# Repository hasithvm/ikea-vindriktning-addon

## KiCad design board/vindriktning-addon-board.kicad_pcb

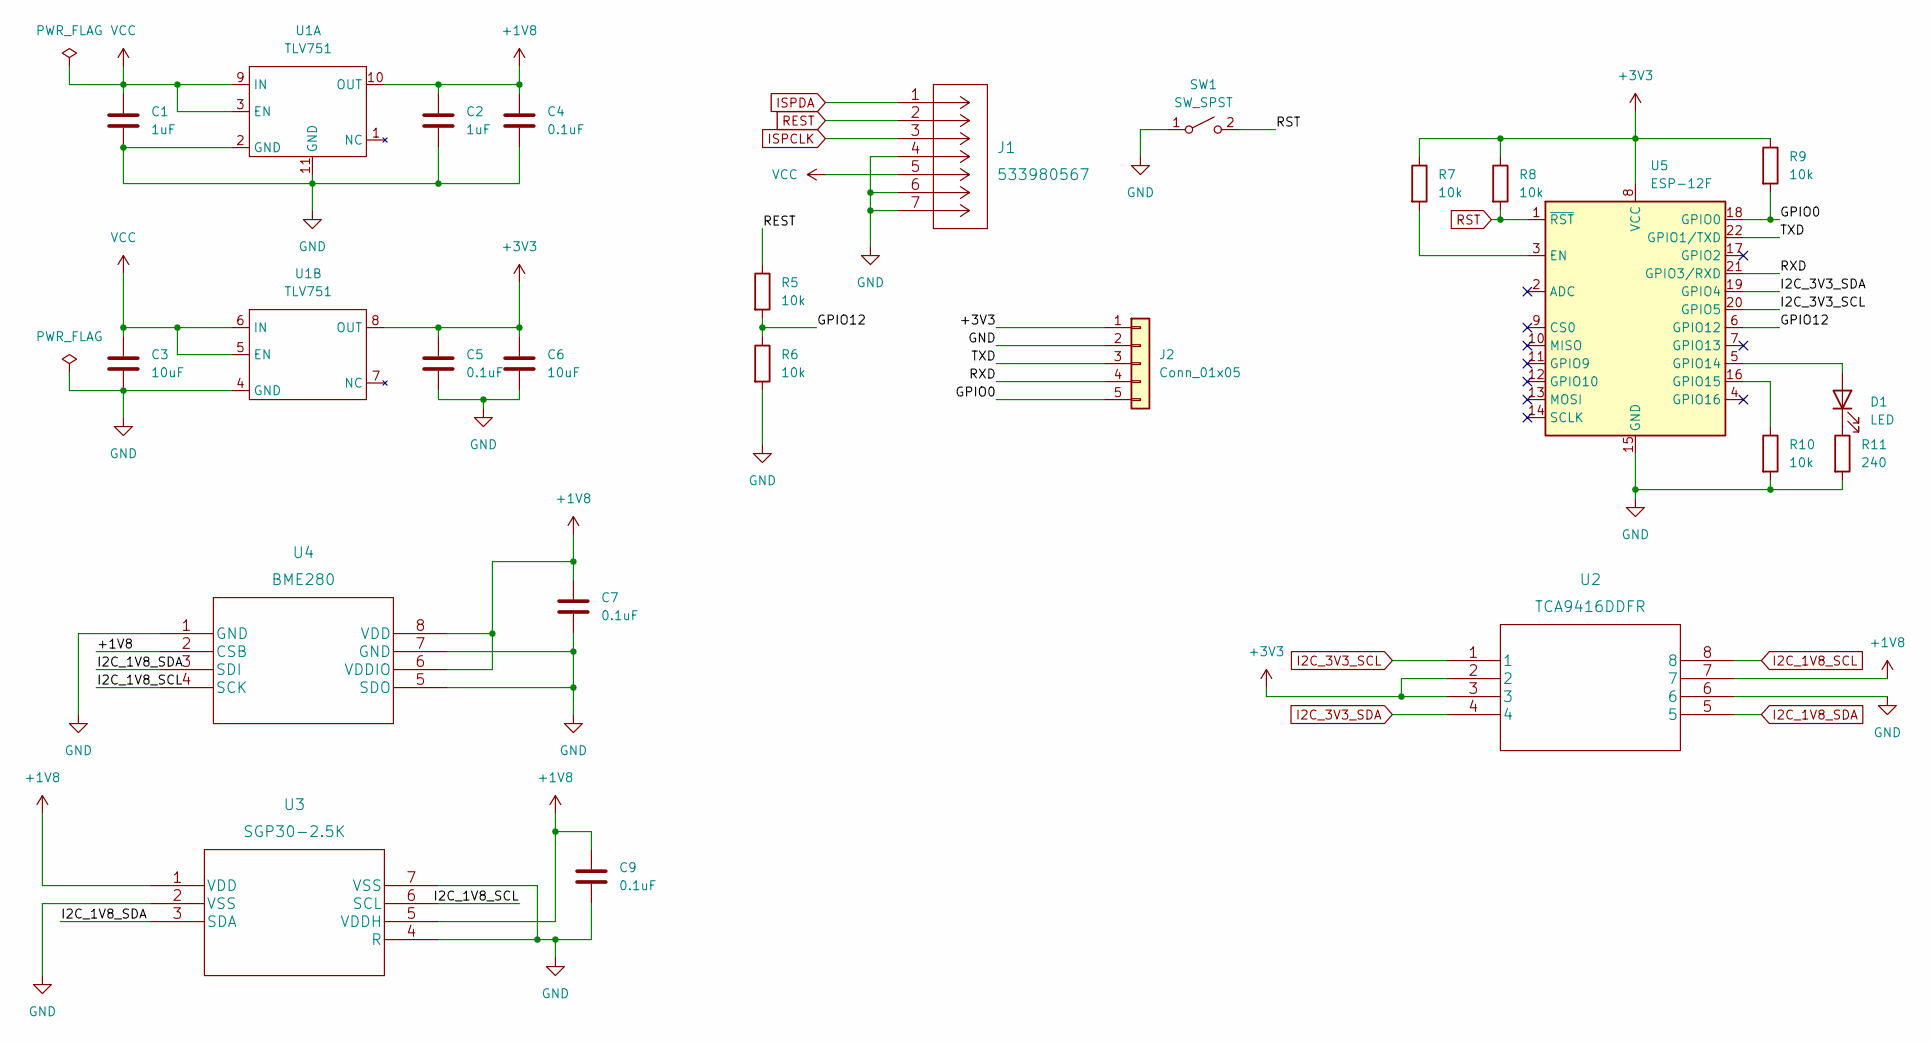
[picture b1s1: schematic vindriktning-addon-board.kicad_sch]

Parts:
C1, C2: 1uF; C_0603_1608Metric
C3, C6: 10uF; C_0805_2012Metric
C4, C5, C7, C9: 0.1uF; C_0603_1608Metric
D1: LED; LED_0603_1608Metric
J1: 533980567
J2: Conn_01x05; PinHeader_1x05_P2.54mm_Vertical
R5, R6, R7, R8, R9, R10: 10k; R_0603_1608Metric
R11: 240; R_0603_1608Metric
SW1: SW_SPST; SW_SPST_EVQP7A
U1: TLV751; TLV75101PDSQR
U2: TCA9416DDFR
U3: SGP30-2.5K
U4: BME280
U5: ESP-12F; ESP-12E

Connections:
+1V8: C2.1, C4.1, C7.1, C9.1, U1.10 (OUT), U2.7, U3.1 (VDD), U3.5 (VDDH), U4.2 (CSB), U4.6 (VDDIO), U4.8 (VDD)
+3V3: C5.1, C6.1, J2.1, R7.1, R8.1, R9.1, U1.8 (OUT), U2.2, U2.3, U5.8 (VCC)
/GPIO0: J2.5, R9.2, U5.18 (GPIO0)
/GPIO12: R5.2, R6.1, U5.6 (GPIO12)
/RXD: J2.4, U5.21 (GPIO3/RXD)
/TXD: J2.3, U5.22 (GPIO1/TXD)
GND: C1.2, C2.2, C3.2, C4.2, C5.2, C6.2, C7.2, C9.2, J1.4, J1.6, J1.7, J2.2, R6.2, R10.2, R11.2, SW1.1 (A), U1.2 (GND), U1.4 (GND), U1.11 (GND), U2.6, U3.2 (VSS), U3.4 (R), U3.7 (VSS), U4.1 (GND), U4.5 (SDO), U4.7 (GND), U5.15 (GND)
I2C_1V8_SCL: U2.8, U3.6 (SCL), U4.4 (SCK)
I2C_1V8_SDA: U2.5, U3.3 (SDA), U4.3 (SDI)
I2C_3V3_SCL: U2.1, U5.20 (GPIO5)
I2C_3V3_SDA: U2.4, U5.19 (GPIO4)
ISPCLK: J1.3
ISPDA: J1.1
unnamed: D1.1 (K), R11.1
unnamed: D1.2 (A), U5.5 (GPIO14)
unnamed: R7.2, U5.3 (EN)
unnamed: R10.1, U5.16 (GPIO15)
REST: J1.2, R5.1
RST: R8.2, SW1.2 (B), U5.1 (~RST)
VCC: C1.1, C3.1, J1.5, U1.3 (EN), U1.5 (EN), U1.6 (IN), U1.9 (IN)

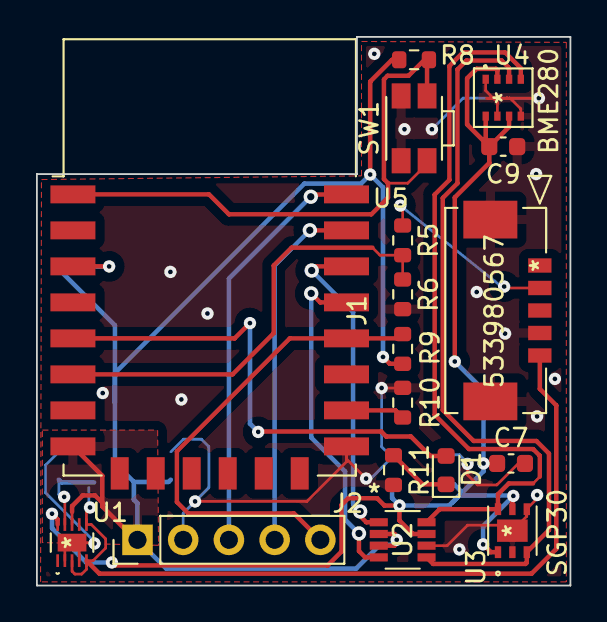
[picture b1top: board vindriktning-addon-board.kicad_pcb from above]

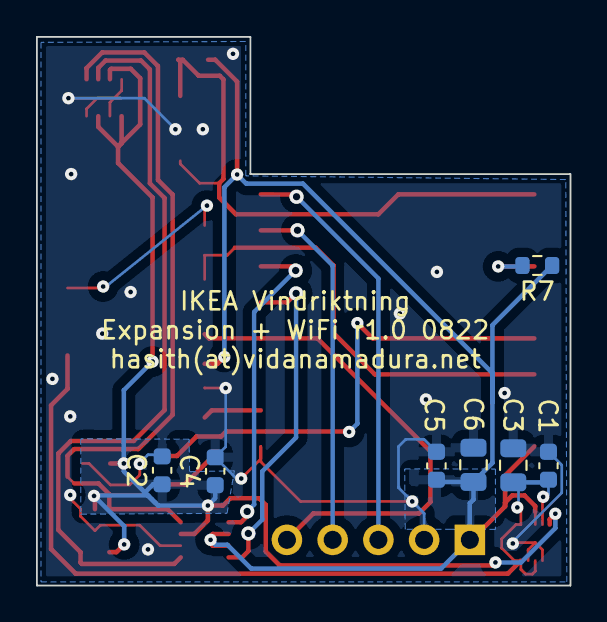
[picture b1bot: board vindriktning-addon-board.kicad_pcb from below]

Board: 2 copper layers, 29.6 x 30.5 mm, 24 parts (7 on the bottom side), 18 nets.

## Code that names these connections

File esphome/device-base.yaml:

# Base YAML config for the Vindriktning add-on board
i2c:
  sda: GPIO4
  scl: GPIO5
  scan: true
  id: bus_sensors

uart:
  rx_pin: GPIO12
  baud_rate: 9600
  id: bus_softuart

sensor:
  - platform: pm1006
    pm_2_5:
      name: "PM2.5"
    uart_id: bus_softuart

  - platform: bme280
    temperature:
      name: "temperature"
      oversampling: 16x
    pressure:
      name: "pressure"
    humidity:
      name: "humidity"
    address: 0x76
    update_interval: 60s
    
  - platform: sgp30
    eco2:
      name: "eCO2"
      accuracy_decimals: 1
    tvoc:
      name: "TVOC"
      accuracy_decimals: 1
    store_baseline: yes
    address: 0x58
    update_interval: 1s

light:
  - platform: status_led
    id: status_indicator
    pin: GPIO14

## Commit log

2022-11-13 v1 of board design, fabbed via OSHPark
2022-11-13 Adding README and licenses
2022-11-13 Updating README to fix image path
2022-11-15 Adding device base YAML file
2022-11-25 updated base YAML for esphome config

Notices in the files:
parts and their libraries:
Copyright 2021 Accelerated Designs. All rights reserved.
